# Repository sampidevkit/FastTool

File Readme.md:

# SAMPI FAST TOOLS

# 1. Breakboard

# 2. FTDI-VCP

# 3. TAG-VCP

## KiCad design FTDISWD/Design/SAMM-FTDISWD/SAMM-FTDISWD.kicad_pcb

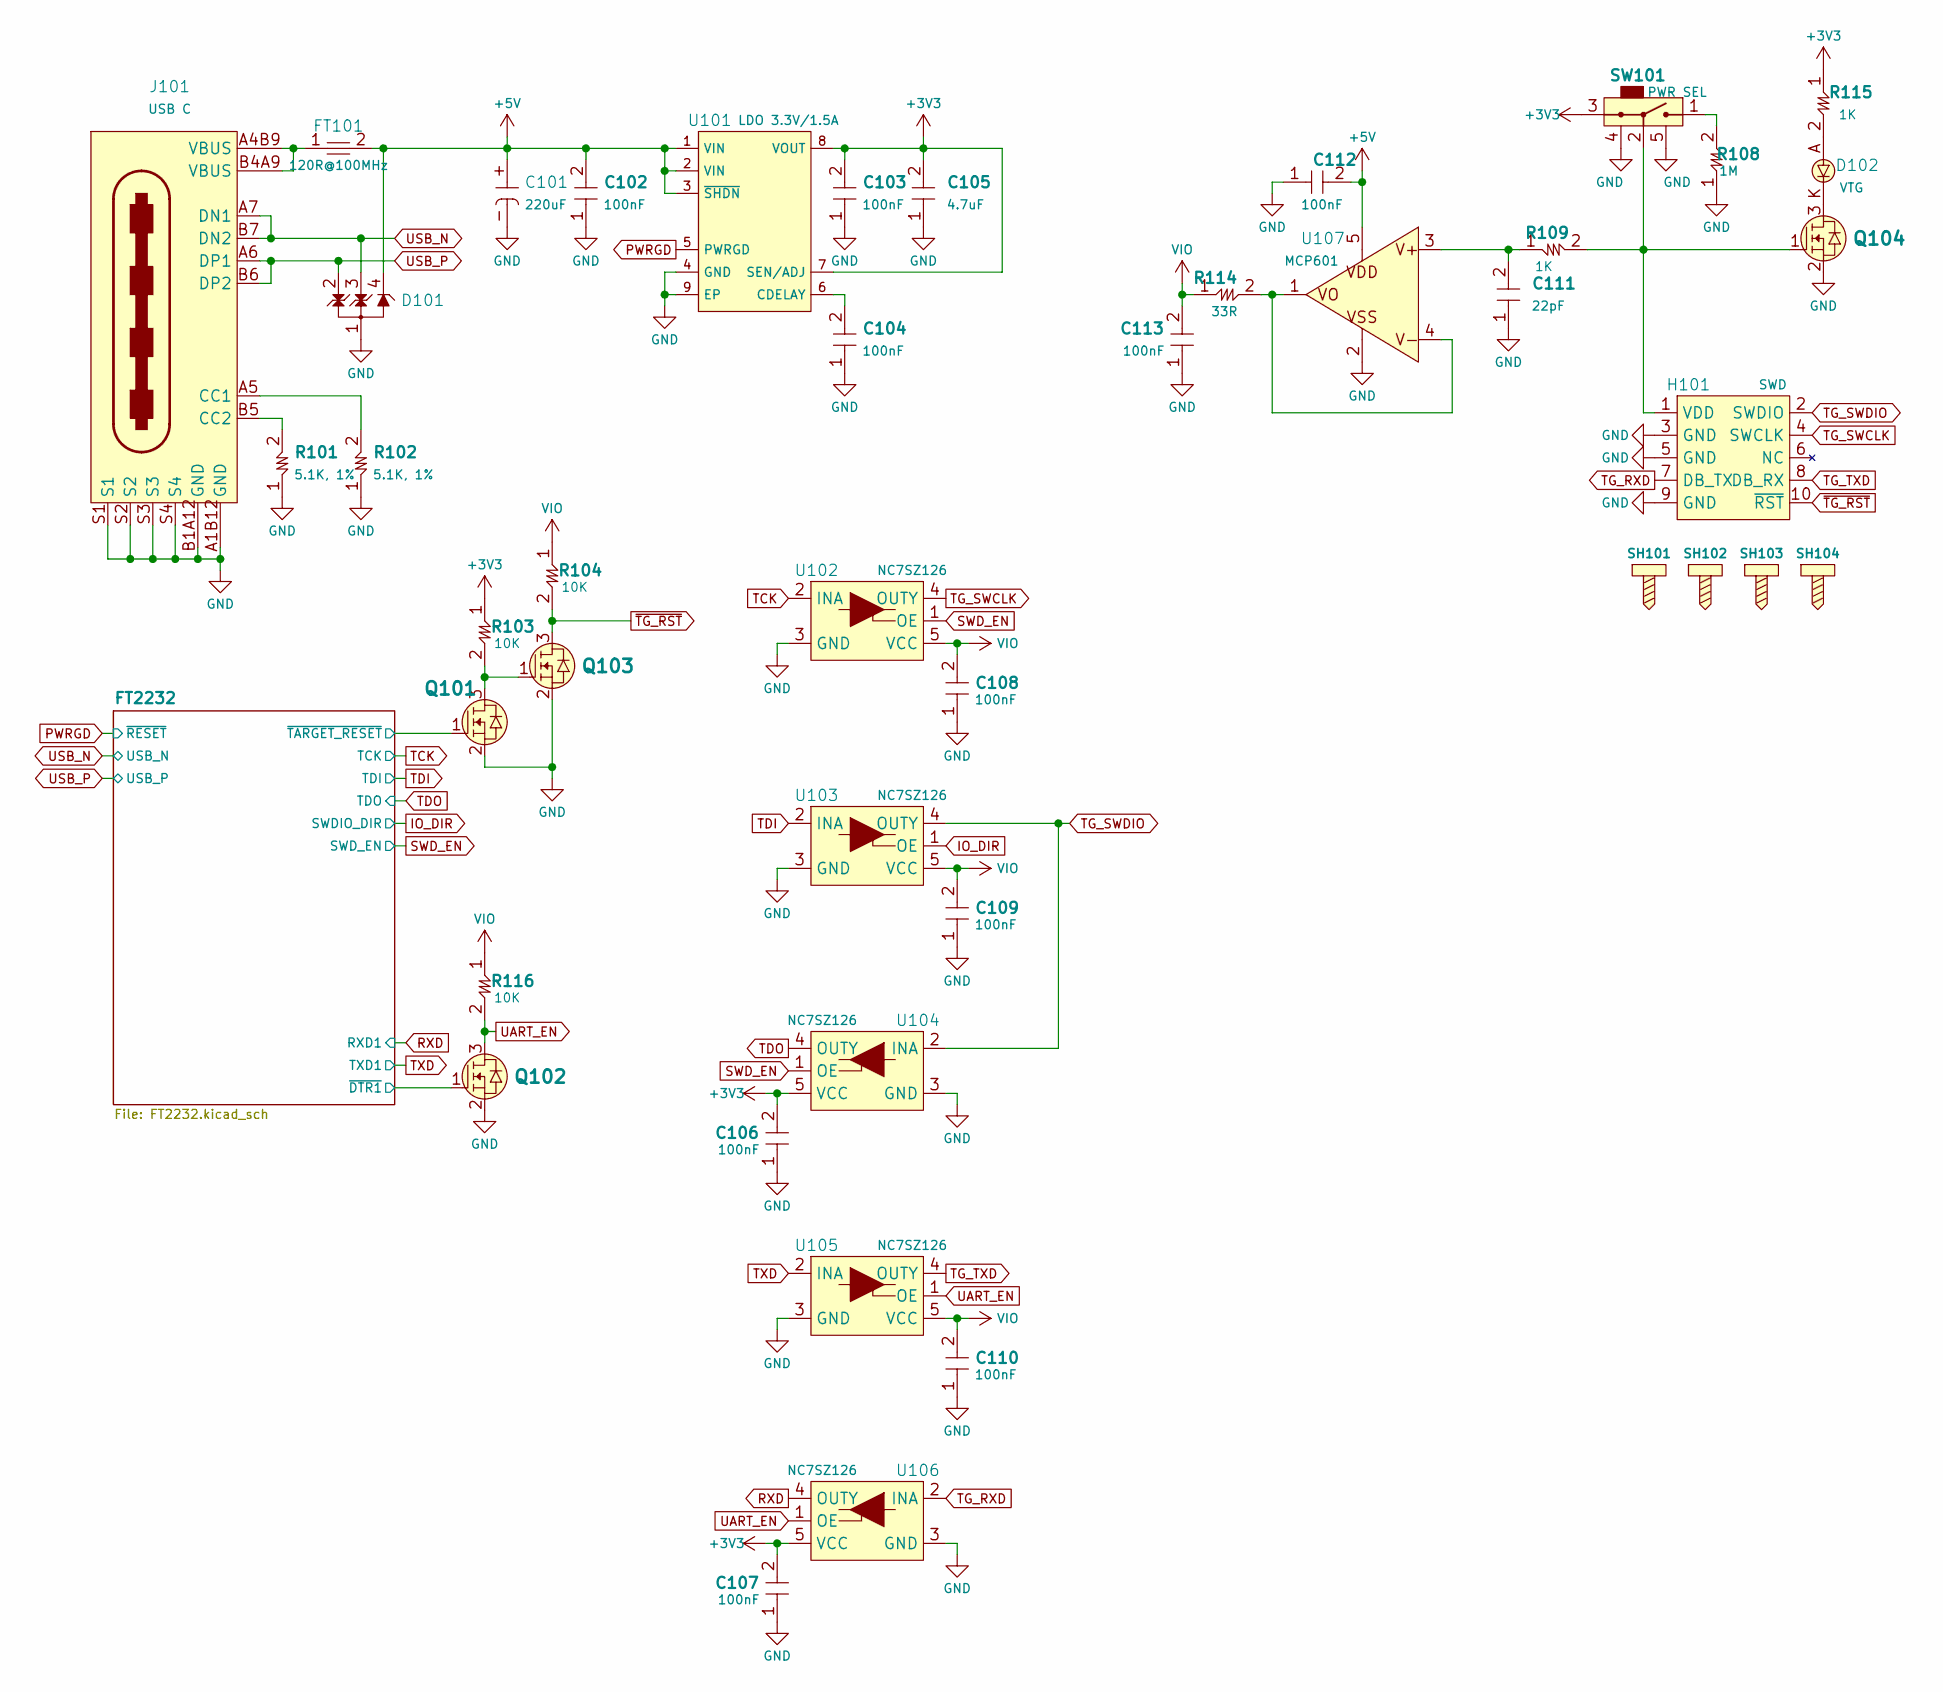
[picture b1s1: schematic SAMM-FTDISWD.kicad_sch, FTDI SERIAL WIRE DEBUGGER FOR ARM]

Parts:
C101: 220uF; CAP1411
C102, C103, C104, C106, C107, C108, C109, C110, C112, C113: 100nF; CAP0402
C105: 4.7uF; CAP0402
C111: 22pF; CAP0402
D101: TVS 3-CH; SOT143B_NEXT
D102: VTG; LED0603
FT101: 120R@100MHz; FB0402
H101: SWD; HDM-2x5x1.27-TH
J101: USB C; USB4105
Q101, Q102, Q103, Q104: MFET N; SOT-723
R101, R102: 5.1K, 1%; RES0402
R103, R104, R116: 10K; RES0402
R108: 1M; RES0402
R109, R115: 1K; RES0402
R114: 33R; RES0402
SH101, SH102, SH103, SH104: SCREW HOLDER; HOLDER-1.5MM
SW101: PWR SEL; CUS-12B
U101: LDO 3.3V/1.5A; DFN8_3x3_MCHP
U102, U103, U104, U105, U106: NC7SZ126; SOT353
U107: MCP601; SOT-23-5_MCHP

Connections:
+3V3: C103.2, C105.2, C106.2, C107.2, R103.1, R115.1, SW101.3 (NO), U101.7 (SEN/ADJ), U101.8 (VOUT), U104.5 (VCC), U106.5 (VCC); also elsewhere on the board
+5V: C101.+, C102.2, C112.2, D101.4 (CH3), FT101.2, U101.1 (VIN), U101.2 (VIN), U101.3 (~SHDN), U107.5 (VDD)
/FT2232/~DTR1: Q102.1 (G); also elsewhere on the board
/FT2232/~TARGET_RESET: Q101.1 (G); also elsewhere on the board
GND: C101.-, C102.1, C103.1, C104.1, C105.1, C106.1, C107.1, C108.1, C109.1, C110.1, C111.1, C112.1, C113.1, D101.1 (GND), H101.3 (GND), H101.5 (GND), H101.9 (GND), J101.A1B12 (GND), J101.B1A12 (GND), J101.S1, J101.S2, J101.S3, J101.S4, Q101.2 (S), Q102.2 (S), Q103.2 (S), Q104.2 (S), R101.1, R102.1, R108.1, SW101.4 (CH), SW101.5 (CH), U101.4 (GND), U101.9 (EP), U102.3 (GND), U103.3 (GND), U104.3 (GND), U105.3 (GND), U106.3 (GND), U107.2 (VSS); also elsewhere on the board
IO_DIR: U103.1 (OE); also elsewhere on the board
unnamed: D102.A, R115.2
unnamed: FT101.1, J101.A4B9 (VBUS), J101.B4A9 (VBUS)
unnamed: H101.1 (VDD), Q104.1 (G), R109.2, SW101.2 (COM)
unnamed: J101.A5 (CC1), R102.2
unnamed: J101.B5 (CC2), R101.2
unnamed: Q101.3 (D), Q103.1 (G), R103.2
unnamed: D102.K, Q104.3 (D)
unnamed: R108.2, SW101.1 (NC)
unnamed: C104.2, U101.6 (CDELAY)
unnamed: C111.2, R109.1, U107.3 (VIN+)
unnamed: R114.2, U107.1 (VOUT), U107.4 (VIN-)
PWRGD: U101.5 (PWRGD); also elsewhere on the board
RXD: U106.4 (OUTY); also elsewhere on the board
SWD_EN: U102.1 (OE), U104.1 (OE); also elsewhere on the board
TCK: U102.2 (INA); also elsewhere on the board
TDI: U103.2 (INA); also elsewhere on the board
TDO: U104.4 (OUTY); also elsewhere on the board
TG_RXD: H101.7 (DB_TX), U106.2 (INA)
TG_SWCLK: H101.4 (SWCLK), U102.4 (OUTY)
TG_SWDIO: H101.2 (SWDIO), U103.4 (OUTY), U104.2 (INA)
TG_TXD: H101.8 (DB_RX), U105.4 (OUTY)
TXD: U105.2 (INA); also elsewhere on the board
UART_EN: Q102.3 (D), R116.2, U105.1 (OE), U106.1 (OE)
USB_N: D101.3 (CH2), J101.A7 (DN1), J101.B7 (DN2); also elsewhere on the board
USB_P: D101.2 (CH1), J101.A6 (DP1), J101.B6 (DP2); also elsewhere on the board
VIO: C108.2, C109.2, C110.2, C113.2, R104.1, R114.1, R116.1, U102.5 (VCC), U103.5 (VCC), U105.5 (VCC)
~TG_RST: H101.10 (~RST), Q103.3 (D), R104.2

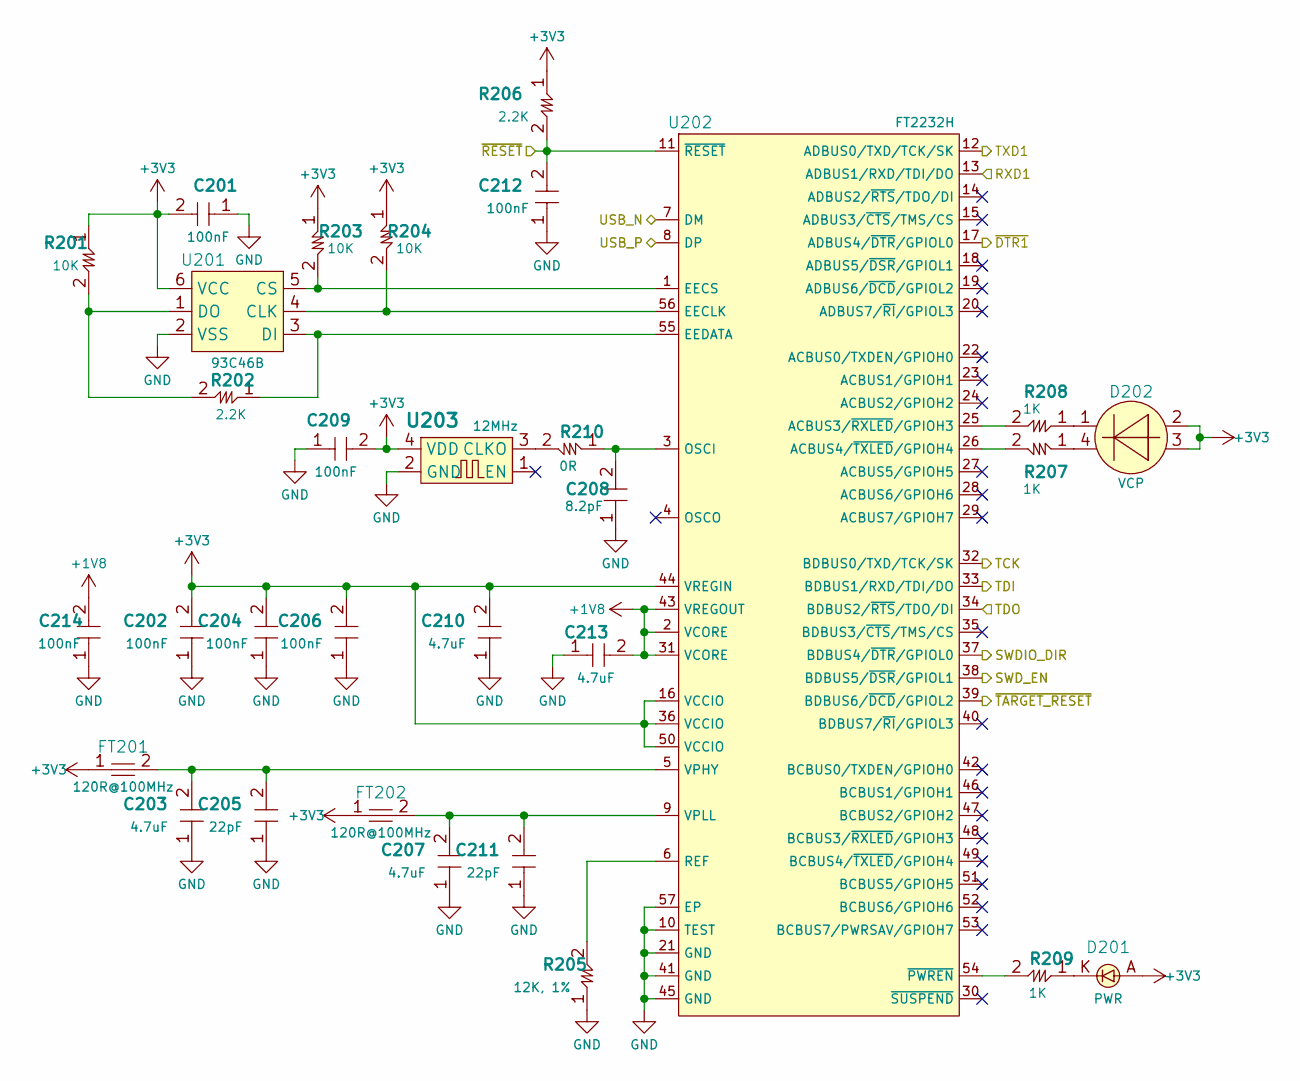
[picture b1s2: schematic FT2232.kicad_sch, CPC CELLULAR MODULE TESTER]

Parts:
C201, C202, C204, C206, C209, C212, C214: 100nF; CAP0402
C203, C207, C210, C213: 4.7uF; CAP0402
C205, C211: 22pF; CAP0402
C208: 8.2pF; CAP0402
D201: PWR; LED0603
D202: VCP; LED0606_4P
FT201, FT202: 120R@100MHz; FB0402
R201, R203, R204: 10K; RES0402
R202, R206: 2.2K; RES0402
R205: 12K, 1%; RES0402
R207, R208, R209: 1K; RES0402
R210: 0R; RES0402
U201: 93C46B; SOT-23-6_MCHP
U202: FT2232H; VQFN-56_FTDI
U203: 12MHz; CDFN2520-ABM10

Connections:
+1V8: C213.2, C214.2, U202.2 (VCORE), U202.31 (VCORE), U202.43 (VREGOUT)
+3V3: C201.2, C202.2, C204.2, C206.2, C209.2, C210.2, D201.A, D202.2 (GA), D202.3 (RA), FT201.1, FT202.1, R201.1, R203.1, R204.1, R206.1, U201.6 (VCC), U202.16 (VCCIO), U202.36 (VCCIO), U202.44 (VREGIN), U202.50 (VCCIO), U203.4 (VDD); also elsewhere on the board
/FT2232/~DTR1: U202.17 (ADBUS4/~DTR/GPIOL0); also elsewhere on the board
/FT2232/~TARGET_RESET: U202.39 (BDBUS6/~DCD/GPIOL2); also elsewhere on the board
GND: C201.1, C202.1, C203.1, C204.1, C205.1, C206.1, C207.1, C208.1, C209.1, C210.1, C211.1, C212.1, C213.1, C214.1, R205.1, U201.2 (VSS), U202.10 (TEST), U202.21 (GND), U202.41 (GND), U202.45 (GND), U202.57 (EP), U203.2 (GND); also elsewhere on the board
IO_DIR: U202.37 (BDBUS4/~DTR/GPIOL0); also elsewhere on the board
unnamed: D201.K, R209.1
unnamed: D202.1 (GK), R208.1
unnamed: D202.4 (RK), R207.1
unnamed: R204.2, U201.4 (CLK), U202.56 (EECLK)
unnamed: R203.2, U201.5 (CS), U202.1 (EECS)
unnamed: R202.1, U201.3 (DI), U202.55 (EEDATA)
unnamed: R201.2, R202.2, U201.1 (DO)
unnamed: R208.2, U202.25 (ACBUS3/~RXLED/GPIOH3)
unnamed: R207.2, U202.26 (ACBUS4/~TXLED/GPIOH4)
unnamed: C208.2, R210.1, U202.3 (OSCI)
unnamed: R205.2, U202.6 (REF)
unnamed: C203.2, C205.2, FT201.2, U202.5 (VPHY)
unnamed: C207.2, C211.2, FT202.2, U202.9 (VPLL)
unnamed: R209.2, U202.54 (~PWREN)
unnamed: R210.2, U203.3 (CLKO)
PWRGD: C212.2, R206.2, U202.11 (~RESET); also elsewhere on the board
RXD: U202.13 (ADBUS1/RXD/TDI/DO); also elsewhere on the board
SWD_EN: U202.38 (BDBUS5/~DSR/GPIOL1); also elsewhere on the board
TCK: U202.32 (BDBUS0/TXD/TCK/SK); also elsewhere on the board
TDI: U202.33 (BDBUS1/RXD/TDI/DO); also elsewhere on the board
TDO: U202.34 (BDBUS2/~RTS/TDO/DI); also elsewhere on the board
TXD: U202.12 (ADBUS0/TXD/TCK/SK); also elsewhere on the board
USB_N: U202.7 (DM); also elsewhere on the board
USB_P: U202.8 (DP); also elsewhere on the board

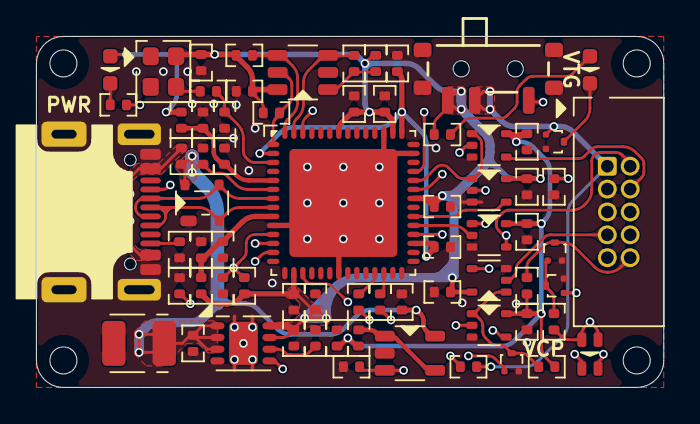
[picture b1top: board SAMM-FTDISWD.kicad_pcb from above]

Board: 4 copper layers, 34.9 x 19.5 mm, 74 parts (0 on the bottom side), 49 nets.

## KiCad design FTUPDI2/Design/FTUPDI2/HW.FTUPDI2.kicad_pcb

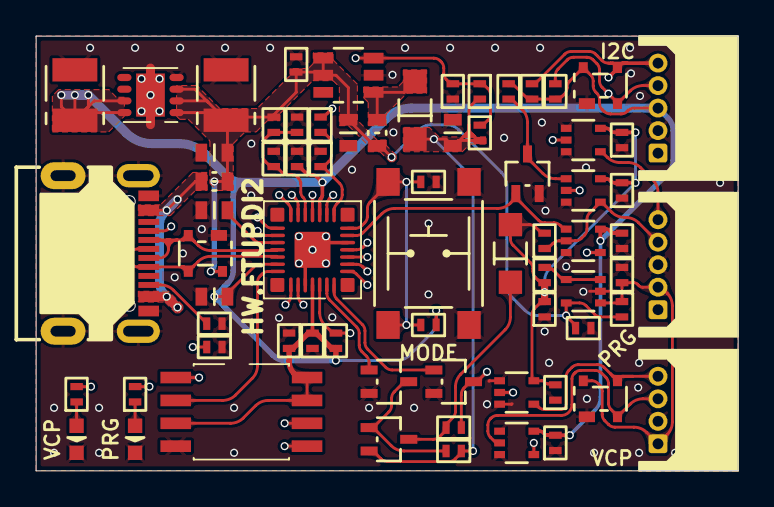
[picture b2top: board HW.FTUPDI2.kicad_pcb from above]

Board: 4 copper layers, 39.0 x 24.1 mm, 70 parts (0 on the bottom side), 45 nets.

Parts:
C1, C9, C11, C14, C17, C18, C20, C21, C23, C24, C25: 100nF; CAP0402
C2, C12, C13, C19, C22: 1nF; CAP0402
C3, C7: 220uF; CAP1411
C4, C5, C6, C8, C10: 10uF; CAP0603
D1, D6: 200mA/0.45VF; SOD-123FL
D2, D5, D7: TVS 5V; SOT143B_NEXT
D3: VCP; LED0603
D4: PRG; LED0603
FT1: 100R@100MHz; FT0603
J1: USB C; USB4105-GF-A
J2: I2C; HDM-1x5x1.25-THRA
J3: PRG; HDM-1x5x1.25-THRA
J5: VCP; HDM-1x4x1.25-THRA
L1: 10uH/0.3A; IND0603
Q1, Q4, Q5: MFET N; SC70-3_SOT-323
Q2: MFET P; SC70-3_SOT-323
R1: 71.5K; RES0402
R2, R3, R4, R5, R12, R19, R20: 5.1K; RES0402
R6, R7, R10, R11, R21: 10K; RES0402
R8: 100R; RES0402
R9, R24: 100K; RES0402
R14, R15: 1K; RES0402
R22: 10R; RES0402
S1: MODE; SW6x6-G
U1: PIC32MM0064GPM028; UQFN28-4x4-EP
U2: MT3608; SOT-23-6_MCHP
U3: 3V3/1.5A; DFN8_3x3_MCHP
U4, U5, U6, U8, U9: LEVEL SHIFTER 1-CH; SOT353
U7: OP-1CH; SOT353
U10: 4MBIT; SOIC8-5.3

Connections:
+3V3: C7.+, C9.2, C10.2, C11.2, C14.2, C17.2, C25.2, D7.4 (CH3), J2.3, R7.1, R10.2, R19.1, R20.2, R21.1, U1.10 (VDD), U1.20 (VUSB3V3), U1.25 (AVDD/VDD), U3.7 (SEN/ADJ), U3.8 (VOUT), U4.5 (VCC), U9.5 (VCC), U10.3 (~WP), U10.7 (~HOLD), U10.8 (VDD)
+5V: C1.2, C3.+, C4.2, C6.2, C21.2, D2.4 (CH3), FT1.1, L1.1, R5.2, R24.2, U2.4 (EN), U2.5 (IN), U3.1 (VIN), U3.2 (VIN), U3.3 (~SHDN), U7.5 (VDD)
/HVP_EN: Q1.1 (G), U1.27 (PGEC2/VREF+/CVREF+/AN0/RP1/OCM1E/INT3/R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)
/LED_PRG: R15.2, U1.16 (PGEC3/TDO/RP18/ASCL1/T3CK/T3G/USBOEN/SD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)
/LED_VCP: R14.2, U1.15 (TMS/REFCLKI/RP14/SDA1/T1CK/T1G/T2CK/T2G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)
/MEM_CLK: U1.13 (RP12/SDA3/SDI3/OCM3F/RB7), U10.6 (SCK)
/MEM_SDI: U1.21 (AN8/LVDIN/RP15/SCL3/SCK3/OCM3A/RB13), U10.2 (SO)
/MEM_SDO: U1.11 (PGED3/RP11/ASDA1/USBID/SS3/FSYNC3/OCM3E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), U10.5 (SI)
/PGC/SCL: D7.3 (CH2), J2.5, R20.1, U1.2 (PGEC1/AN3/C1INC/C2INA/RP7/OCM2D/RB1)
/PGD/SDA: D7.2 (CH1), J2.4, R19.2, U1.1 (PGED1/AN2/C1IND/C2INB/C3INC/RP6/OCM2C/R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)
/PROGRAMMER/VIO_SEN: C22.2, D5.4 (CH3), J3.2, J5.1, R24.1, U7.1 (VIN+)
/PROGRAMMER/~PROG_RST: J3.1, Q4.3 (D), R8.1
/PROG_CLK: U1.9 (SOSCO/SCLKI/RP5/PWRLCLK/OCM3D/RA4), U6.2 (INA)
/PROG_DIR: Q5.1 (G), U1.6 (OSC1/CLKI/AN5/RP3/OCM1C/RA2), U9.1 (~OE)
/PROG_RST: Q4.1 (G), U1.28 (PGED2/VREF-/AN1/RP2/OCM1F/RA1)
/PROG_RXD: U1.3 (AN4/C1INB/RP8/SDA2/OCM2E/RB2), U9.4 (OUTY)
/PROG_TXD: U1.4 (TDI/AN11/C1INA/RP9/SCL2/OCM2F/RB3), U8.2 (INA)
/RXD1: U1.23 (AN10/C3INA/REFCLKO/RP17/U1RX/SS1/FSYNC1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), U4.4 (OUTY)
/TXD1: U1.22 (CVREF/AN9/C3INB/RP16/RTCC/U1TX/VBUSON/S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), U5.2 (INA)
/USB_N: D2.2 (CH1), J1.A7 (DN1), J1.B7 (DN2), U1.18 (D-/RB10)
/USB_P: D2.3 (CH2), J1.A6 (DP1), J1.B6 (DP2), U1.19 (D+/RB11)
/USB_VBUS: C12.2, R5.1, R6.1, U1.12 (VBUS/RB6)
/VPP_DIV: C13.2, R11.2, U1.8 (SOSCI/AN7/RP10/OCM3C/RB4)
/~BT_MOD: C19.2, R21.2, S1.1, S1.3, U1.7 (OSC2/CLKO/AN6/C3IND/RP4/OCM1D/RA3)
/~MCLR: J2.1, R7.2, U1.26 (MCLR)
/~MEM_CS: U1.14 (TCK/RP13/SCL1/U1CTS/SCK1/OCM1A/RB8), U10.1 (~CE)
GND: C1.1, C3.-, C4.1, C5.1, C6.1, C7.-, C8.1, C9.1, C10.1, C11.1, C12.1, C13.1, C14.1, C17.1, C18.1, C19.1, C20.1, C21.1, C22.1, C23.1, C24.1, C25.1, D2.1 (GND), D3.K, D4.K, D5.1 (GND), D7.1 (GND), J1.A1_B12 (GND), J1.B1_A12 (GND), J1.S1 (EP), J1.S2 (EP), J1.S3 (EP), J1.S4 (EP), J2.2, J3.3, J5.2, Q1.2 (S), Q4.2 (S), Q5.2 (S), R2.1, R3.1, R4.1, R6.2, S1.2, S1.4, U1.5 (VSS), U1.24 (AVSS/VSS), U1.29 (EP), U2.2 (GND), U3.4 (GND), U3.9 (EP), U4.1 (~OE), U4.3 (GND), U5.1 (~OE), U5.3 (GND), U6.1 (~OE), U6.3 (GND), U7.2 (VSS), U8.3 (GND), U9.3 (GND), U10.4 (GND)
unnamed: D3.A, R14.1
unnamed: D4.A, R15.1
unnamed: D5.2 (CH1), J5.3, U4.2 (INA)
unnamed: D5.3 (CH2), J5.4, U5.4 (OUTY)
unnamed: FT1.2, J1.A4_B9 (VBUS), J1.B4_A9 (VBUS)
unnamed: J1.A5 (CC1), R4.2
unnamed: J1.B5 (CC2), R3.2
unnamed: Q1.3 (D), Q2.1 (G), R9.1
unnamed: D6.K, Q2.3 (D), R8.2
unnamed: Q5.3 (D), R10.1, U8.1 (~OE)
unnamed: C8.2, U1.17 (VCAP)
unnamed: C2.1, R1.1, R2.2, R11.1, U2.3 (FB)
unnamed: D1.A, L1.2, U2.1 (SW)
unnamed: J3.5, U6.4 (OUTY)
unnamed: R22.1, U7.3 (VIN-), U7.4 (VOUT)
unnamed: J3.4, R12.1, U8.4 (OUTY), U9.2 (INA)
VPP: C2.2, C5.2, D1.K, Q2.2 (S), R1.2, R9.2
VTG: C18.2, C20.2, C23.2, C24.2, D6.A, R12.2, R22.2, U5.5 (VCC), U6.5 (VCC), U8.5 (VCC)

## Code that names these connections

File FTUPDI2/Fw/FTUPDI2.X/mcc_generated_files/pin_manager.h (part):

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*/
/**
  @Summary
    Sets the GPIO pin, RA0, high using LATA0.

  @Description
    Sets the GPIO pin, RA0, high using LATA0.

  @Preconditions
    The RA0 must be set to an output.
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#define HVP_EN_SetHigh()          ( LATASET = (1 << 0) )
/**
  @Summary
    Sets the GPIO pin, RA0, low using LATA0.

  @Description
    Sets the GPIO pin, RA0, low using LATA0.

  @Preconditions
    The RA0 must be set to an output.
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    Sets a value to the GPIO pin.

  @Description
    Sets or Resets the GPIO pin, RA0, low or high using LATA0.

  @Preconditions
    The RA0 must be set to an output.
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
/**
  @Summary
    Toggles the GPIO pin, RA0, using LATA0.

  @Description
    Toggles the GPIO pin, RA0, using LATA0.

  @Preconditions
    The RA0 must be set to an output.
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#define HVP_EN_Toggle()           ( LATAINV = (1 << 0) )
/**
  @Summary
    Reads the value of the GPIO pin, RA0.

  @Description
    Reads the value of the GPIO pin, RA0.

  @Preconditions
    None.
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    </code>

*/
#define HVP_EN_GetValue()         PORTAbits.RA0
/**
  @Summary
    Configures the GPIO pin, RA0, as an input.

  @Description
    Configures the GPIO pin, RA0, as an input.

  @Preconditions
    None.
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#define HVP_EN_SetDigitalInput()   ( TRISASET = (1 << 0) )
/**
  @Summary
    Configures the GPIO pin, RA0, as an output.

  @Description
    Configures the GPIO pin, RA0, as an output.

  @Preconditions
    None.
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#define HVP_EN_SetDigitalOutput()   ( TRISACLR = (1 << 0) )
/**
  @Summary
    Sets the GPIO pin, RA1, high using LATA1.

  @Description
    Sets the GPIO pin, RA1, high using LATA1.

  @Preconditions
    The RA1 must be set to an output.
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#define PROG_RST_SetHigh()          ( LATASET = (1 << 1) )
/**
  @Summary
    Sets the GPIO pin, RA1, low using LATA1.

  @Description
    Sets the GPIO pin, RA1, low using LATA1.

  @Preconditions
    The RA1 must be set to an output.
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    Sets a value to the GPIO pin.

  @Description
    Sets or Resets the GPIO pin, RA1, low or high using LATA1.

  @Preconditions
    The RA1 must be set to an output.
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
/**
  @Summary
    Toggles the GPIO pin, RA1, using LATA1.

  @Description
    Toggles the GPIO pin, RA1, using LATA1.

  @Preconditions
    The RA1 must be set to an output.
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#define PROG_RST_Toggle()           ( LATAINV = (1 << 1) )
/**
  @Summary
    Reads the value of the GPIO pin, RA1.

  @Description
    Reads the value of the GPIO pin, RA1.

  @Preconditions
    None.
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    </code>

*/
#define PROG_RST_GetValue()         PORTAbits.RA1
/**
  @Summary
    Configures the GPIO pin, RA1, as an input.

  @Description
    Configures the GPIO pin, RA1, as an input.

  @Preconditions
    None.
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#define PROG_RST_SetDigitalInput()   ( TRISASET = (1 << 1) )
/**
  @Summary
    Configures the GPIO pin, RA1, as an output.

  @Description
    Configures the GPIO pin, RA1, as an output.

  @Preconditions
    None.
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#define PROG_RST_SetDigitalOutput()   ( TRISACLR = (1 << 1) )
/**
  @Summary
    Sets the GPIO pin, RA2, high using LATA2.

  @Description
    Sets the GPIO pin, RA2, high using LATA2.

  @Preconditions
    The RA2 must be set to an output.
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#define PROG_DIR_SetHigh()          ( LATASET = (1 << 2) )
/**
  @Summary
    Sets the GPIO pin, RA2, low using LATA2.

  @Description
    Sets the GPIO pin, RA2, low using LATA2.

  @Preconditions
    The RA2 must be set to an output.
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    Sets a value to the GPIO pin.

  @Description
    Sets or Resets the GPIO pin, RA2, low or high using LATA2.

  @Preconditions
    The RA2 must be set to an output.
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
/**
  @Summary
    Toggles the GPIO pin, RA2, using LATA2.

  @Description
    Toggles the GPIO pin, RA2, using LATA2.

  @Preconditions
    The RA2 must be set to an output.
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#define PROG_DIR_Toggle()           ( LATAINV = (1 << 2) )
/**
  @Summary
    Reads the value of the GPIO pin, RA2.

  @Description
    Reads the value of the GPIO pin, RA2.

  @Preconditions
    None.
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    </code>

*/
#define PROG_DIR_GetValue()         PORTAbits.RA2
/**
  @Summary
    Configures the GPIO pin, RA2, as an input.

  @Description
    Configures the GPIO pin, RA2, as an input.

  @Preconditions
    None.
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#define PROG_DIR_SetDigitalInput()   ( TRISASET = (1 << 2) )
/**
  @Summary
    Configures the GPIO pin, RA2, as an output.

  @Description
    Configures the GPIO pin, RA2, as an output.

  @Preconditions
    None.
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#define PROG_DIR_SetDigitalOutput()   ( TRISACLR = (1 << 2) )
/**
  @Summary
    Sets the GPIO pin, RA3, high using LATA3.

  @Description
    Sets the GPIO pin, RA3, high using LATA3.

  @Preconditions
    The RA3 must be set to an output.
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#define BT_MODE_N_SetHigh()          ( LATASET = (1 << 3) )
/**
  @Summary
    Sets the GPIO pin, RA3, low using LATA3.

  @Description
    Sets the GPIO pin, RA3, low using LATA3.

  @Preconditions
    The RA3 must be set to an output.
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    Sets a value to the GPIO pin.

  @Description
    Sets or Resets the GPIO pin, RA3, low or high using LATA3.

  @Preconditions
    The RA3 must be set to an output.
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
/**
  @Summary
    Toggles the GPIO pin, RA3, using LATA3.

  @Description
    Toggles the GPIO pin, RA3, using LATA3.

  @Preconditions
    The RA3 must be set to an output.
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#define BT_MODE_N_Toggle()           ( LATAINV = (1 << 3) )
/**
  @Summary
    Reads the value of the GPIO pin, RA3.

  @Description
    Reads the value of the GPIO pin, RA3.

  @Preconditions
    None.
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    </code>

*/
#define BT_MODE_N_GetValue()         PORTAbits.RA3
/**
  @Summary
    Configures the GPIO pin, RA3, as an input.

  @Description
    Configures the GPIO pin, RA3, as an input.

  @Preconditions
    None.
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#define BT_MODE_N_SetDigitalInput()   ( TRISASET = (1 << 3) )
/**
  @Summary
    Configures the GPIO pin, RA3, as an output.

  @Description
    Configures the GPIO pin, RA3, as an output.

  @Preconditions
    None.
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#define BT_MODE_N_SetDigitalOutput()   ( TRISACLR = (1 << 3) )
/**
  @Summary
    Sets the GPIO pin, RA4, high using LATA4.

  @Description
    Sets the GPIO pin, RA4, high using LATA4.

  @Preconditions
    The RA4 must be set to an output.
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#define PROG_CLK_SetHigh()          ( LATASET = (1 << 4) )
/**
  @Summary
    Sets the GPIO pin, RA4, low using LATA4.

  @Description
    Sets the GPIO pin, RA4, low using LATA4.

  @Preconditions
    The RA4 must be set to an output.
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    Sets a value to the GPIO pin.

  @Description
    Sets or Resets the GPIO pin, RA4, low or high using LATA4.

  @Preconditions
    The RA4 must be set to an output.
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
/**
  @Summary
    Toggles the GPIO pin, RA4, using LATA4.

  @Description
    Toggles the GPIO pin, RA4, using LATA4.

  @Preconditions
    The RA4 must be set to an output.
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#define PROG_CLK_Toggle()           ( LATAINV = (1 << 4) )
/**
  @Summary
    Reads the value of the GPIO pin, RA4.

  @Description
    Reads the value of the GPIO pin, RA4.

  @Preconditions
    None.
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    </code>

*/
#define PROG_CLK_GetValue()         PORTAbits.RA4
/**
  @Summary
    Configures the GPIO pin, RA4, as an input.

  @Description
    Configures the GPIO pin, RA4, as an input.

  @Preconditions
    None.
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#define PROG_CLK_SetDigitalInput()   ( TRISASET = (1 << 4) )
/**
  @Summary
    Configures the GPIO pin, RA4, as an output.

  @Description
    Configures the GPIO pin, RA4, as an output.

  @Preconditions
    None.
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#define PROG_CLK_SetDigitalOutput()   ( TRISACLR = (1 << 4) )
/**
  @Summary
    Sets the GPIO pin, RB0, high using LATB0.

  @Description
    Sets the GPIO pin, RB0, high using LATB0.

  @Preconditions
    The RB0 must be set to an output.
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#define SW_SDA_SetHigh()          ( LATBSET = (1 << 0) )
/**
  @Summary
    Sets the GPIO pin, RB0, low using LATB0.

  @Description
    Sets the GPIO pin, RB0, low using LATB0.

  @Preconditions
    The RB0 must be set to an output.
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    Sets a value to the GPIO pin.

  @Description
    Sets or Resets the GPIO pin, RB0, low or high using LATB0.

  @Preconditions
    The RB0 must be set to an output.
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
/**
  @Summary
    Toggles the GPIO pin, RB0, using LATB0.

  @Description
    Toggles the GPIO pin, RB0, using LATB0.

  @Preconditions
    The RB0 must be set to an output.
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#define SW_SDA_Toggle()           ( LATBINV = (1 << 0) )
/**
  @Summary
    Reads the value of the GPIO pin, RB0.

  @Description
    Reads the value of the GPIO pin, RB0.

  @Preconditions
    None.
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    </code>

*/
#define SW_SDA_GetValue()         PORTBbits.RB0
/**
  @Summary
    Configures the GPIO pin, RB0, as an input.

  @Description
    Configures the GPIO pin, RB0, as an input.

  @Preconditions
    None.
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#define SW_SDA_SetDigitalInput()   ( TRISBSET = (1 << 0) )
/**
  @Summary
    Configures the GPIO pin, RB0, as an output.

  @Description
    Configures the GPIO pin, RB0, as an output.

  @Preconditions
    None.
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#define SW_SDA_SetDigitalOutput()   ( TRISBCLR = (1 << 0) )
/**
  @Summary
    Sets the GPIO pin, RB1, high using LATB1.

  @Description
    Sets the GPIO pin, RB1, high using LATB1.

  @Preconditions
    The RB1 must be set to an output.
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#define SW_SCL_SetHigh()          ( LATBSET = (1 << 1) )
/**
  @Summary
    Sets the GPIO pin, RB1, low using LATB1.
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
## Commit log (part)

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2022-07-24 Initialize
2022-07-24 HW testing application
2022-07-25 USB CDC Debug
2022-07-26 USB CDC Debug: fix RX buffer
2022-07-27 USB_CDC_Debug, USB_CDC_UART
2022-07-28 USB_CDC_UART update 1
2022-07-31 FreeRTOS Kernel V10.2.0
2022-08-09 Add Util lib, fix the USB CDC hangs while closing port
2022-08-10 I2C2 and QWIIC port
2022-08-11 I2C2 and QWIIC port update 1
2022-08-12 I2C2 and QWIIC port update 2
2022-08-12 LED dimmer using PWM
2022-08-16 Remove Library, RTOS, add Loadables
2022-08-16 Add Library sub-module
2022-08-18 update library and linker file
2022-08-21 update RTOS ISR asm libs
2022-08-23 I2C2 and QWIIC port update 3
2022-08-23 I2C2 and QWIIC port update 4
2022-08-23 I2C2 and QWIIC port update 5
2022-08-24 I2C2 and QWIIC port update 6
2022-08-26 I2C2 and QWIIC port update 7
2022-08-26 I2C2 and QWIIC port update 8
2023-02-12 QWIIC ALS31313 demo
2023-02-23 Bootloader update, SIM7020x demo
2023-04-12 SIM7020x update 1
2023-04-13 SIM7020x update 2
2023-04-14 SIM7020x update 3
2023-04-14 SIM7020x update 4
2023-04-14 SIM7020x update 5
2023-04-15 SIM7020x update 6
2023-04-15 NB-IOT DEMO Build: 16:54:47-Apr 15 2023
2023-04-16 SIM7020x update 7
2023-04-17 NB-IOT DEMO Build: 14:13:57-Apr 17 2023
2023-04-18 NB-IOT DEMO Build: 16:57:39-Apr 18 2023
2023-04-28 USB_CDC_UART: press button to trigger RA0
2023-09-08 Update RX, TX led state of USB_CDC_UART
2023-10-13 Production files, Fw Rel Oct132023-231656
2024-09-03 Remove source of fttag64 branch
2024-09-03 FTBRB V0 production files
2024-09-03 FTDI Hw V1.0 source
2024-09-03 Source of FTTAG V1, V2, V3
2024-09-27 FTPRO initialize
2024-09-28 PCB Outline
2025-07-17 FTUPDI2 schematic
2025-07-18 FTUPDI2 layout
2025-08-02 Implement PK3 AVR Fw
2025-08-10 Implement PK3 AVR Fw update 1

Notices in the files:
FTUPDI2/Fw/FTUPDI2.X/mcc_generated_files/pin_manager.h:
(c) 2020 Microchip Technology Inc. and its subsidiaries. You may use this
